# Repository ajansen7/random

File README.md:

# Random Scripts Repository

A collection of various scripts, experiments, and miscellaneous code.

## Projects

### 🧮 Aspens Calculator (`aspens-calculator/`)
- **Purpose**: Computer vision scripts likely for tile or board analysis.
- **Key Tools**: `opencv-python`, `numpy`.
- **Contents**: 
  - Several versions of a calculator (`calc_v*.py`)
  - `training.py` and `training-v2.py` for model training/data collection.
  - `tile-finder.py` for image analysis.

### 🦕 Dino Gen (`dino-gen/`)
- **Purpose**: QR code stitching and image processing, including a Streamlit app.
- **Key Tools**: `streamlit`, `opencv-python`, `pyzbar`.
- **Contents**:
  - `dino_app.py`: Streamlit-based application.
  - `qr_auto_stitch.py`, `qr_manual.py`, `qr_sticter.py`: Tools for QR code processing.

### 🍎 New Fruit (`new-fruit/`)
- **Purpose**: A static web page showcasing fruit/meat hybrids.
- **Key Tools**: HTML, CSS, assets (images and audio).
- **Contents**:
  - `index.html`: The main page.
  - Various image assets like `apple_steak.png` and `banana_sausage.png`.

### 📞 Tattle Phone (`tattle-phone/`)
- **Purpose**: A 3D-printed, toddler-proof 90s-style handset that records "tattles" and uploads them to Google Drive.
- **Key Tools**: ESP32-S3 (Arduino), custom KiCad PCB, Google Apps Script.
- **Contents**:
  - `README.md`: Full design doc (architecture, BOM, power, PCB, enclosure, build plan).
  - `firmware/tattle_phone/`: Record/upload firmware.
  - `cloud/drive_upload.gs`: Drive upload receiver with email notification.

## Setup

### Python Dependencies
To install the necessary Python libraries:

```bash
pip install -r requirements.txt
```

Note: `pyzbar` may require additional system-level libraries (e.g., `libzbar-dev` on Linux or `zbar` via Homebrew on macOS).

## Contributing
Feel free to add your own random scripts or improve existing ones!

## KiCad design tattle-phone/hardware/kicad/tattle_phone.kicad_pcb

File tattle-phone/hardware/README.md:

# Tattle Phone: PCB

There's a KiCad project in [`kicad/`](kicad/). It has a schematic with every part
and connection, and a **routed** board: outline, placement fitted to the printed
case, ~1,800 track segments and ~260 vias, GND pours on both layers and the antenna keep-out.

**6 connections are still open.** They're in tight spots where the autorouter and my
fix-up router couldn't get through without shoving other traces aside. KiCad's
interactive router does that easily. **[KICAD_GUIDE.md](KICAD_GUIDE.md) walks a first-time
user through each one with a close-up picture.** After that, `kicad_gen/make_fab.py`
generates the factory files.

> ⚠️ Component values come from datasheets and common reference designs
> (Adafruit's BQ24075 and MAX98357A boards are worth opening alongside). Check
> them, and the footprints, against current datasheets before ordering. This
> board hasn't been built.

## Files

| File | What it is |
|---|---|
| `kicad/tattle_phone.kicad_pro` | Open this in KiCad 10. It was generated with KiCad 7, so 10 will offer to upgrade it; say yes |
| `kicad/tattle_phone.kicad_sch` | One-sheet schematic. Every pin carries a **net label**, so it reads like a netlist. Matching labels are connected |
| `kicad/tattle_phone.kicad_pcb` | Board: outline, placement, nets, pours, keep-out, net classes |
| `kicad/tattle.kicad_sym` | Project symbol library (only the MAX17048; everything else is stock KiCad) |
| `kicad_gen/design.py` | **The circuit as code:** every part, footprint, pin→net and position. This is the master copy |
| `kicad_gen/build.py` | Regenerates the whole KiCad project from `design.py` + `layout.py` |
| `kicad_gen/check.py` | Compares schematic and board pin by pin, then runs DRC and summarises it |
| `kicad_gen/route.py`, `fixup.py` | Autorouting (FreeRouting) and post-route fix-ups; see "How it was routed" |
| `layout.py` | Dimensions shared by the board **and** the 3D-printed case (keys, LEDs, holes, outline) |
| `place_footprints.py` | Scripting-console helper. Re-snaps the case-critical parts if you move things by hand |

### Two ways to work

- **Edit in KiCad (normal):** open the project, finish the last connections, tidy the
  schematic. From then on the KiCad files are the master copy, and `design.py` becomes reference.
  Don't re-run `build.py`, because it would overwrite your routing.
- **Edit the code:** change `design.py` / `layout.py`, run
  `python3 kicad_gen/build.py && python3 kicad_gen/check.py` (needs KiCad's Python
  module), and you get a fresh project. This is good for big part swaps before routing.

## Finishing the routing (KiCad 10)

Open the board, press **B** to refill the pours, then **Inspect → Design Rules Checker**.
It lists the 6 open connections (case coordinates in mm from the bottom-centre of the board):

| Net | Where | What to do |
|---|---|---|
| VBAT | charger U2, pin 2 (≈ −9.6, 18) | Short hop on the back. Nudge the neighbouring trace with the interactive router (X, then drag) |
| GND | ESD chip D1 (≈ 6, 15) | Add a via next to its GND pin, or run a short trace to the nearest GND via |
| GND | speaker-amp corner (≈ 15, 50) | Same: via or short trace to the pour |
| GND | battery gauge U6 area (≈ 16, 57) | Same |
| GND | LED level shifter U8, pin 3 (≈ 9, 74) | Its pin sits in a pocket. Shove one adjacent trace 0.3 mm and drop a via |
| GND | LED power switch Q2 area (≈ 8, 89) | Same |

Then re-run DRC until "unconnected items" reads 0, and do a visual pass. Pay most
attention to the 3.3 V regulator loop (U3/L1/C4–C6) and the USB pair: the autorouter
gets these right electrically, but you can make them shorter and fatter by hand.

**How it was routed** (all scripted, in `kicad_gen/`): `route.py` runs the
[FreeRouting](https://github.com/freerouting/freerouting) autorouter on everything
except GND. `fixup.py` then finishes the leftover signals with a small A* router
(narrowing to 0.15–0.25 mm at fine-pitch pins), finds GND copper islands by rasterizing
the pours, and ties each island to the main ground with a via or short trace.
`fixup.py --cleanup` removes duplicate and dangling vias. Re-running `build.py`
regenerates an **unrouted** board, so only do that if you want to start over.

## Current check results

- **Schematic vs board:** 377 pins, 71 nets, 0 mismatches. KiCad exported the
  schematic's netlist and it was compared pad by pad with the board.
- **DRC:** no clearance, edge, hole or keep-out errors. What's left:
  - *Unconnected items: 6*. See "Finishing the routing" above.
  - *Courtyard overlap LEDn / SWn (12×):* each key LED sits under its keycap, just
    beside the tact switch. The bodies clear by about 0.25 mm; the switch's outline is drawn
    generously.
  - *Library footprint issues:* footprints were placed from KiCad's install
    folder, not through a library table. KiCad 10 may offer to relink them.
  - *Silkscreen:* `tidy.py` places every reference label clear of pads, other labels
    and the edge, and drops artwork nobody can see (LED outlines under the keycaps). A few
    footprint outlines still touch their own pads; KiCad trims those automatically in the Gerbers.
  - *Starved thermals:* a few QFN centre pads have fewer than two ground spokes until routing
    adds vias under them.

## What's on the board

Front (faces the keypad): the 13 tact switches (through-hole) and the 14 RGB LEDs.
Back: everything else.

| Block | Parts | Notes |
|---|---|---|
| USB-C | J1 HRO TYPE-C-31-M-12 (back, mouth at the bottom edge), R1/R2 5.1k CC pull-downs (separate!), F1 polyfuse, D1 USBLC6 ESD, D2 SMF5.0A TVS | Same port charges and flashes the ESP32 |
| Charger | U2 **BQ24075** (power path + SYSOFF), R3–R8, C1–C3, J2 battery JST-PH, J4 NTC JST-PH | ISET 1.2k ≈ 750 mA charge; ILIM 1.5k ≈ 1 A in; R5 (TMR) left unfitted = default safety timers. BQ24075 instead of BQ24074 because it has the SYSOFF pin the power switch needs |
| Power switch | SW14 PCM12 slide, right edge | Drives SYSOFF: OFF disconnects the battery; charging still works |
| Mode switch | SW17 PCM12 slide, left edge → GPIO38 | **TATTLE** = deep sleep, CALL only; **PLAY** = stay on Wi-Fi for intercom |
| 3.3 V | U3 TPS63001 buck-boost, L1 1.5 µH XAL4020, C4–C7 | Footprint has 0.2 mm thermal vias (board min drill set to 0.2 mm) |
| MCU | U1 ESP32-S3-WROOM-1-N16R8 (back, antenna flush with top edge), C8–C11, R9/R10, SW15 RESET, SW16 BOOT | Antenna keep-out zone: no copper in the top ~6 mm |
| Mic | MK1 ICS-43434 (back) + C12, R11 | Port hole through the board lines up with the case's mic duct |
| Amp | U4 MAX98357A, C13/C14, R12, J3 speaker JST-PH | GAIN tied to VDD = 6 dB. J3 sits low on the right; run the speaker leads up the inside of the case |
| Gauge | U6 MAX17048 + C15, R13–R15 (I2C pull-ups) | I2C 0x36 |
| Keypad | SW1–SW12 + U7 **TCA9555RTWR** (QFN, fits between the switch legs), R16, C16; SW13 CALL + R17 | I2C 0x20, internal pull-ups |
| LEDs | LED1 CALL, LED2–13 keys, **LED14 status light**, all SK6812MINI on the front; Q1/Q2 power gate, U8 74AHCT1G125 level shifter, R18–R20, C17/C18, C20–C33 | Chain order matches the firmware: 0 = CALL, 1–12 = keys, 13 = status |
| Test | TP1 TX, TP2 RX, TP3 GND, TP4 VBAT, TP5 VSYS, TP6 3V3, TP7 spare IO1; FID1–3 | |

The pin map matches [`firmware/tattle_phone/pins.h`](../firmware/tattle_phone/pins.h).

## Ordering (JLCPCB or similar)

- 2-layer, 1.6 mm, any colour. Min drill 0.2 mm (thermal vias under U1/U3).
- **Assembly on both sides** (the LEDs are on the front). That costs a bit more
  than one side, but nothing on this board is novice-friendly to hand-solder
  except the through-hole parts.
- **You solder:** 13 tact switches and 3 JST-PH connectors, all big through-hole
  pins. JLC can do these too for a fee.
- Check stock for: ESP32-S3-WROOM-1-N16R8, BQ24075RGTR, TPS63001DRCR,
  MAX98357AETE+T, ICS-43434, MAX17048G+T10, TCA9555RTWR, SK6812MINI, HRO TYPE-C-31-M-12,
  C&K PCM12SMTR. Swap in equivalents in KiCad if any are out of stock.

## Before ordering

1. Finish the 6 connections above, DRC to zero errors.
2. Export a STEP (File → Export → STEP) and drop it into the enclosure model as a fit check.
3. Fabrication outputs: Gerbers + drill files, BOM, and component placement (CPL). See `../ORDERING.md`.

## Bring-up checklist

1. With no battery, plug in USB. Check VIN, VSYS, PGOOD low, and 3V3.
2. Connect the battery. A USB meter should read ~750 mA charge, CHG low. Check that
   the power switch OFF kills VSYS on battery.
3. Flash over USB-C (hold BOOT, tap RESET the first time).
4. Firmware: check the `rms=` mic levels, a test tone, the LEDs, then an upload.
5. Measure deep-sleep current with the switch on TATTLE. Target < 100 µA.

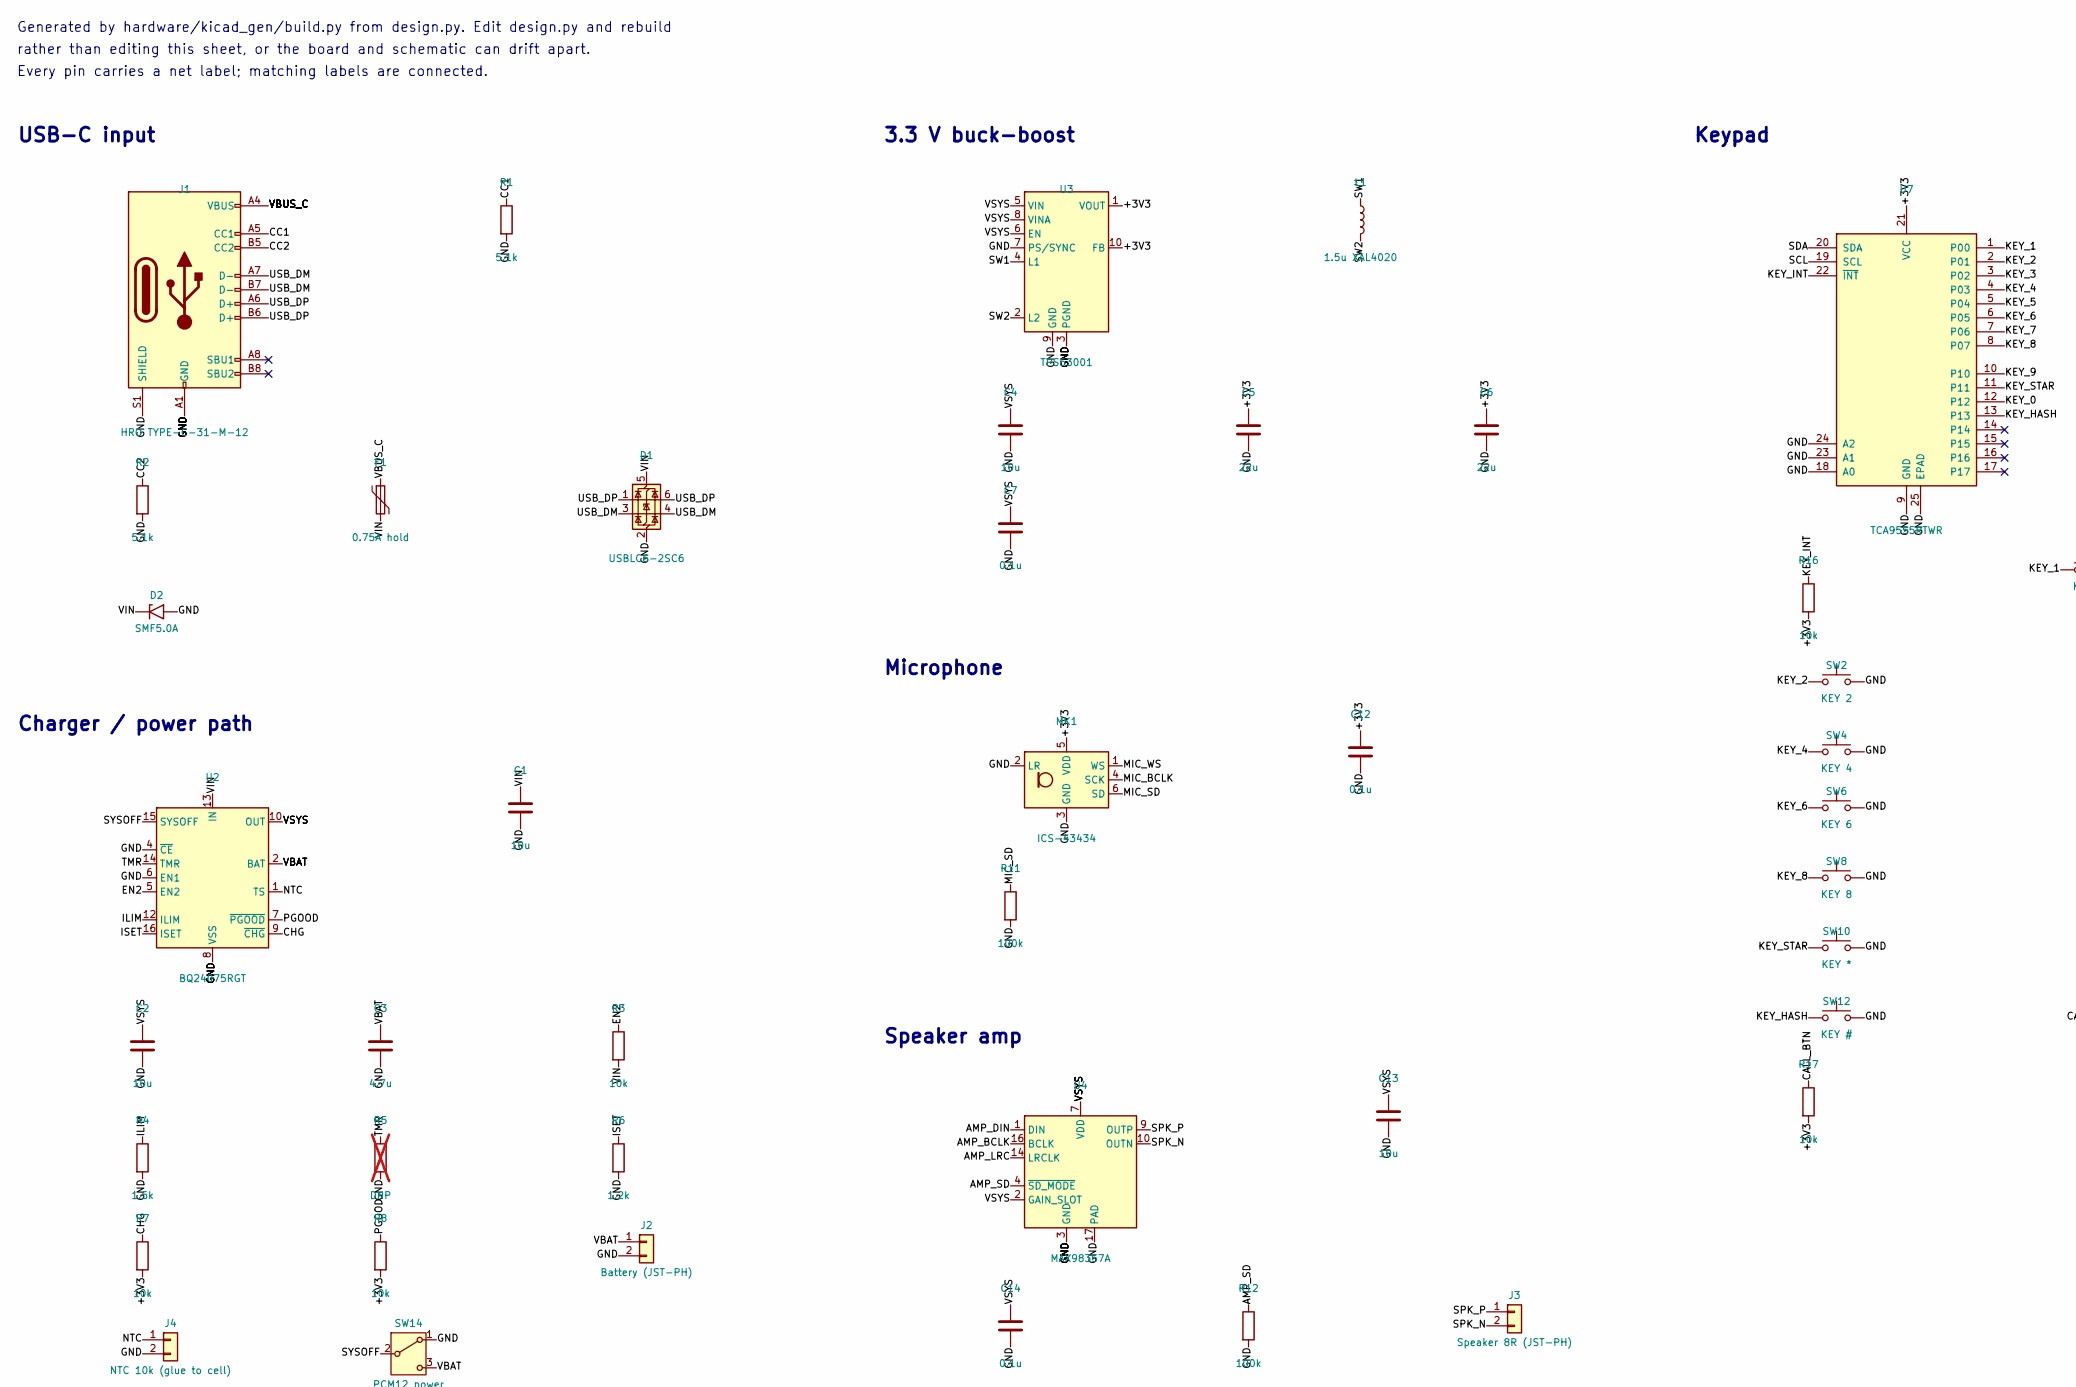
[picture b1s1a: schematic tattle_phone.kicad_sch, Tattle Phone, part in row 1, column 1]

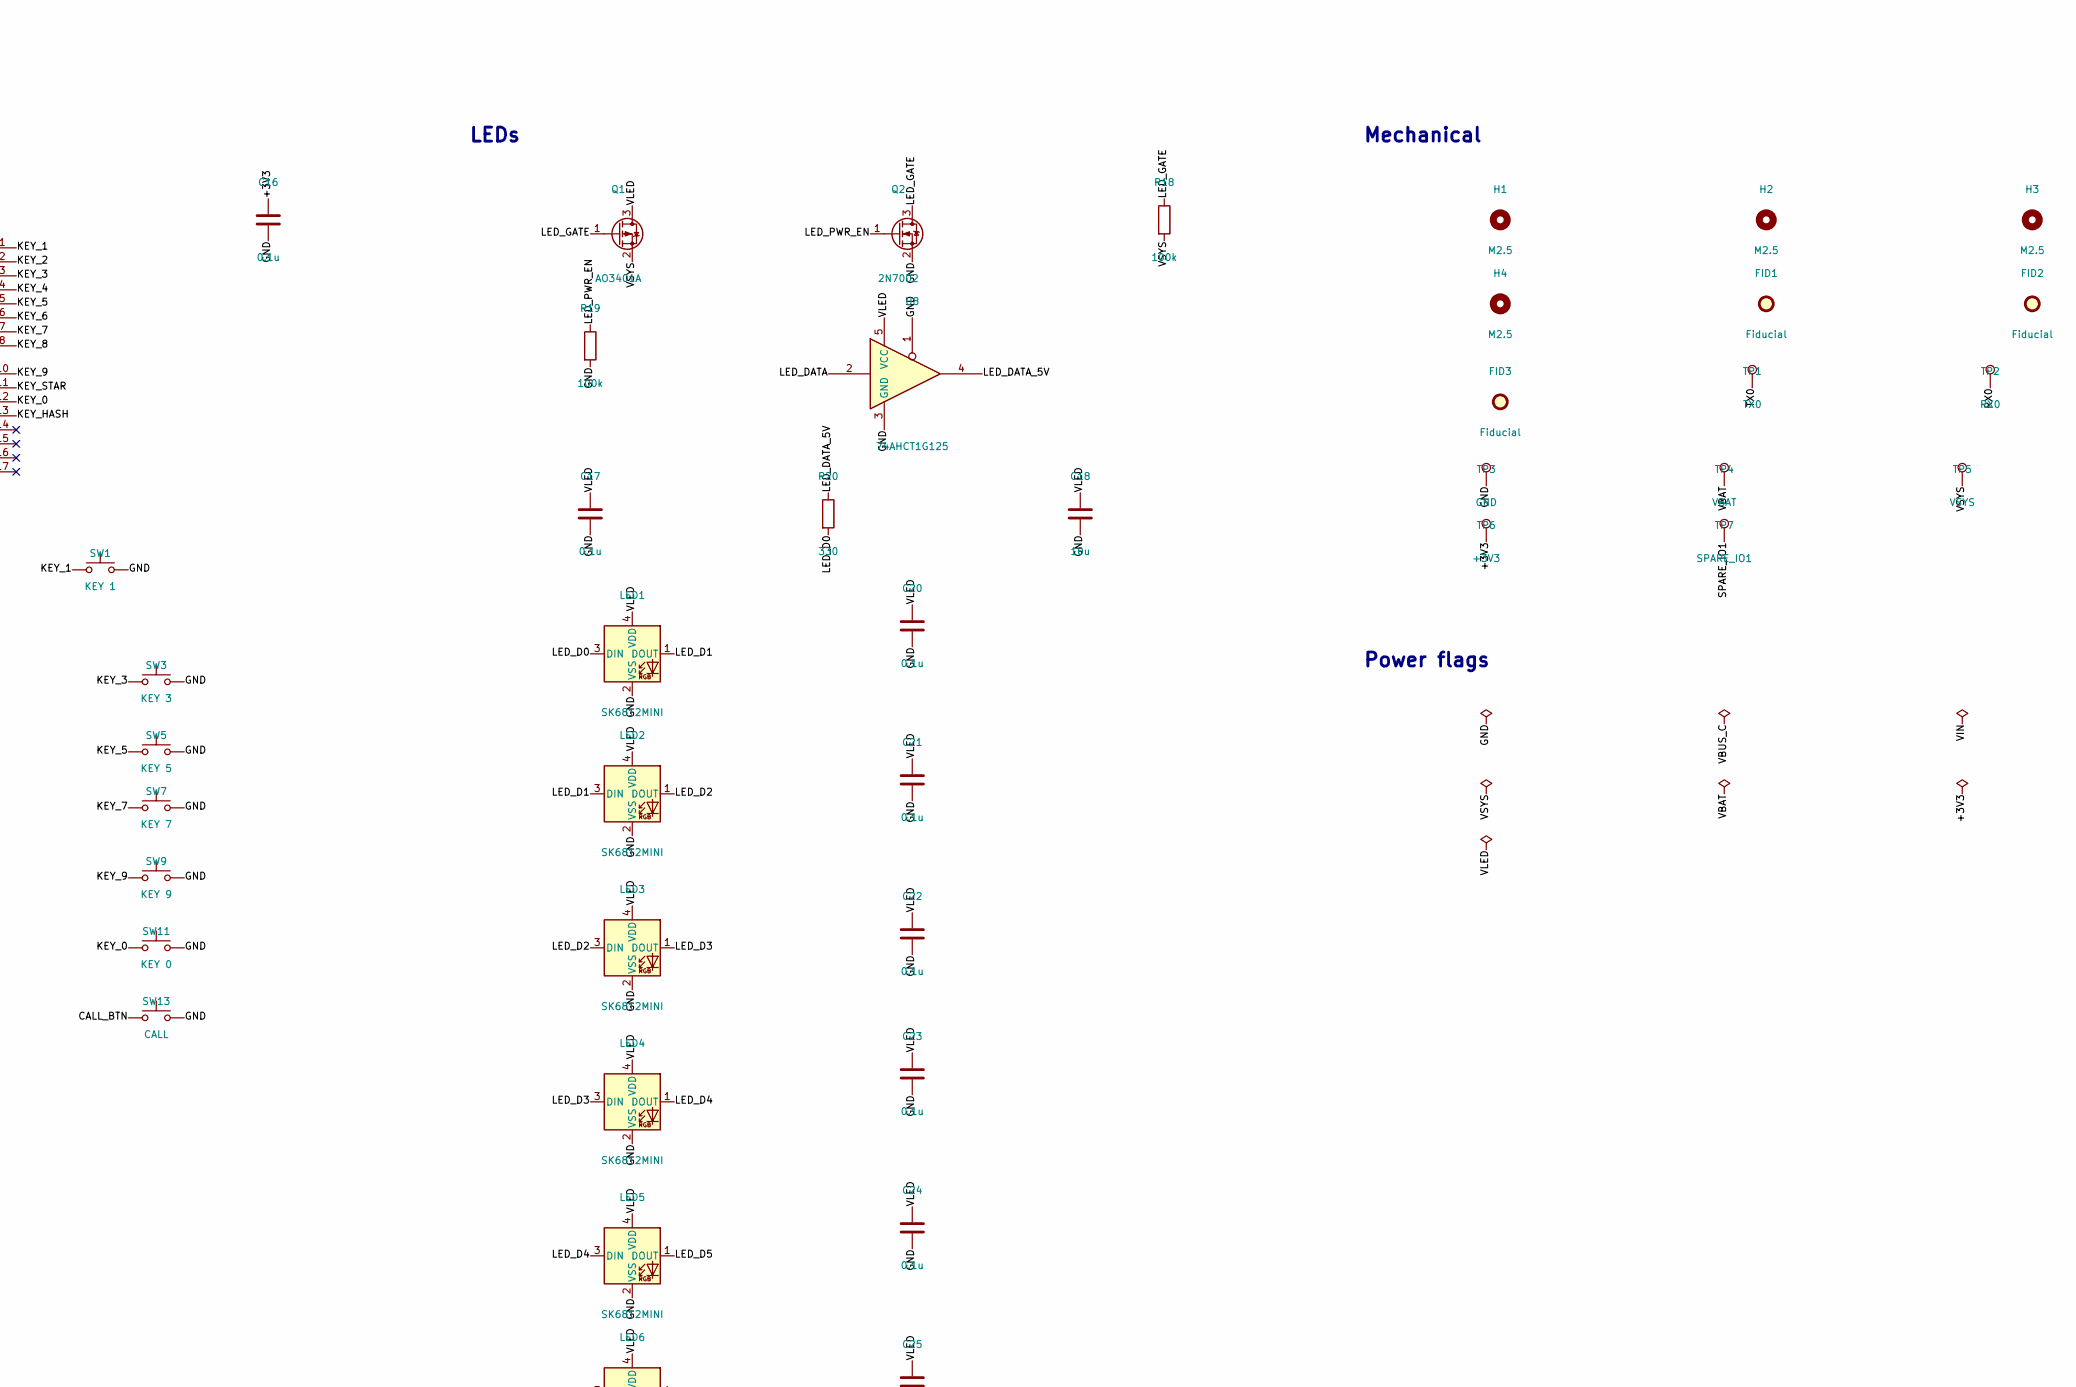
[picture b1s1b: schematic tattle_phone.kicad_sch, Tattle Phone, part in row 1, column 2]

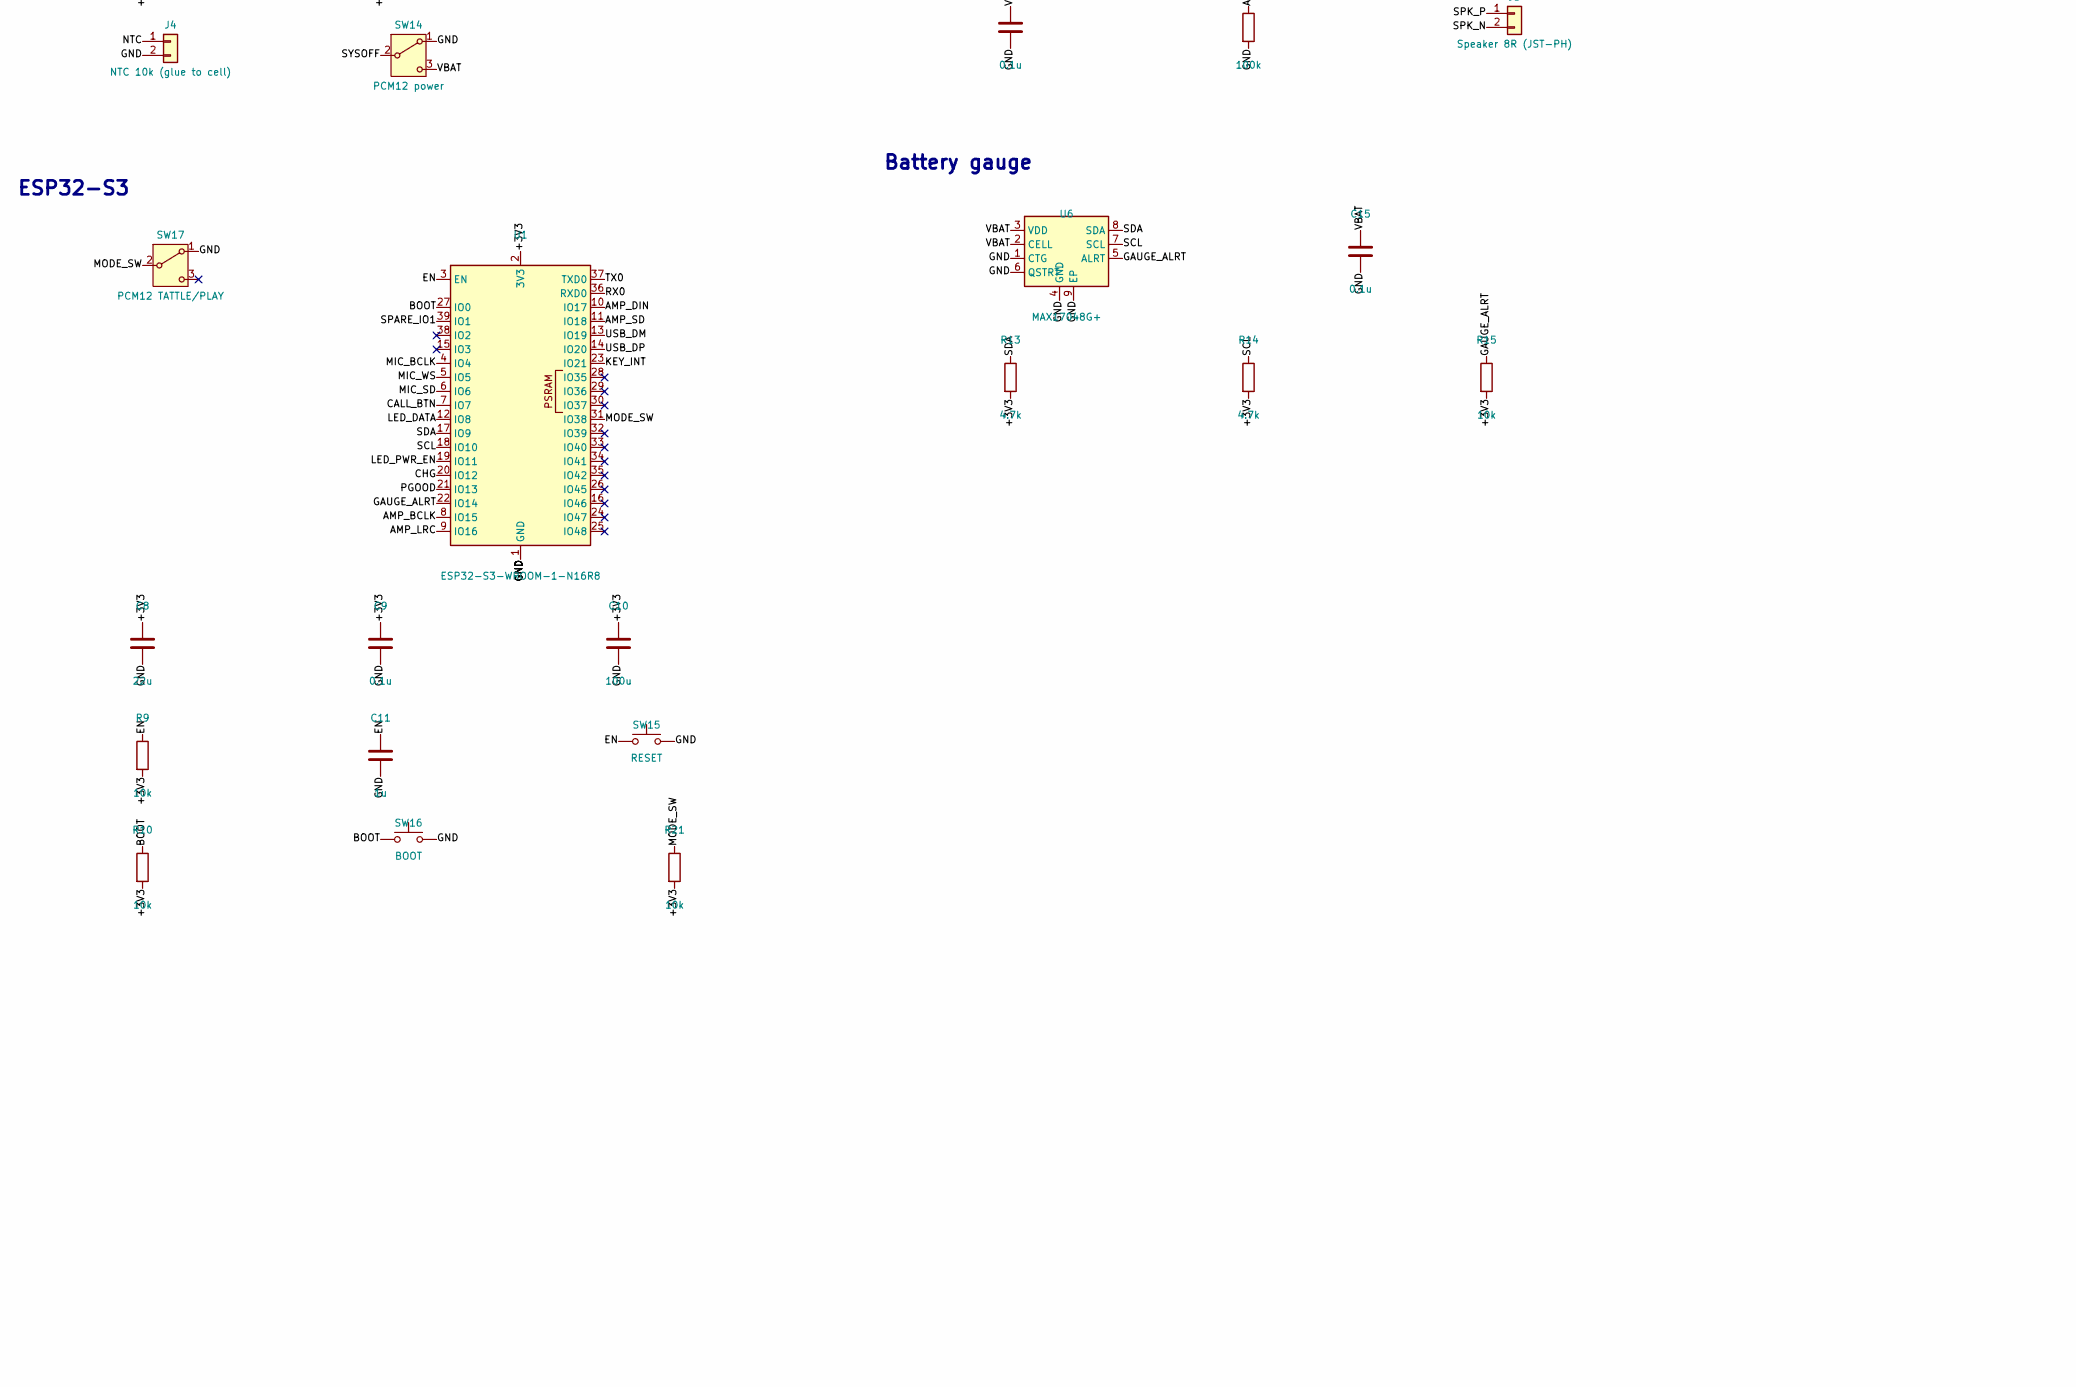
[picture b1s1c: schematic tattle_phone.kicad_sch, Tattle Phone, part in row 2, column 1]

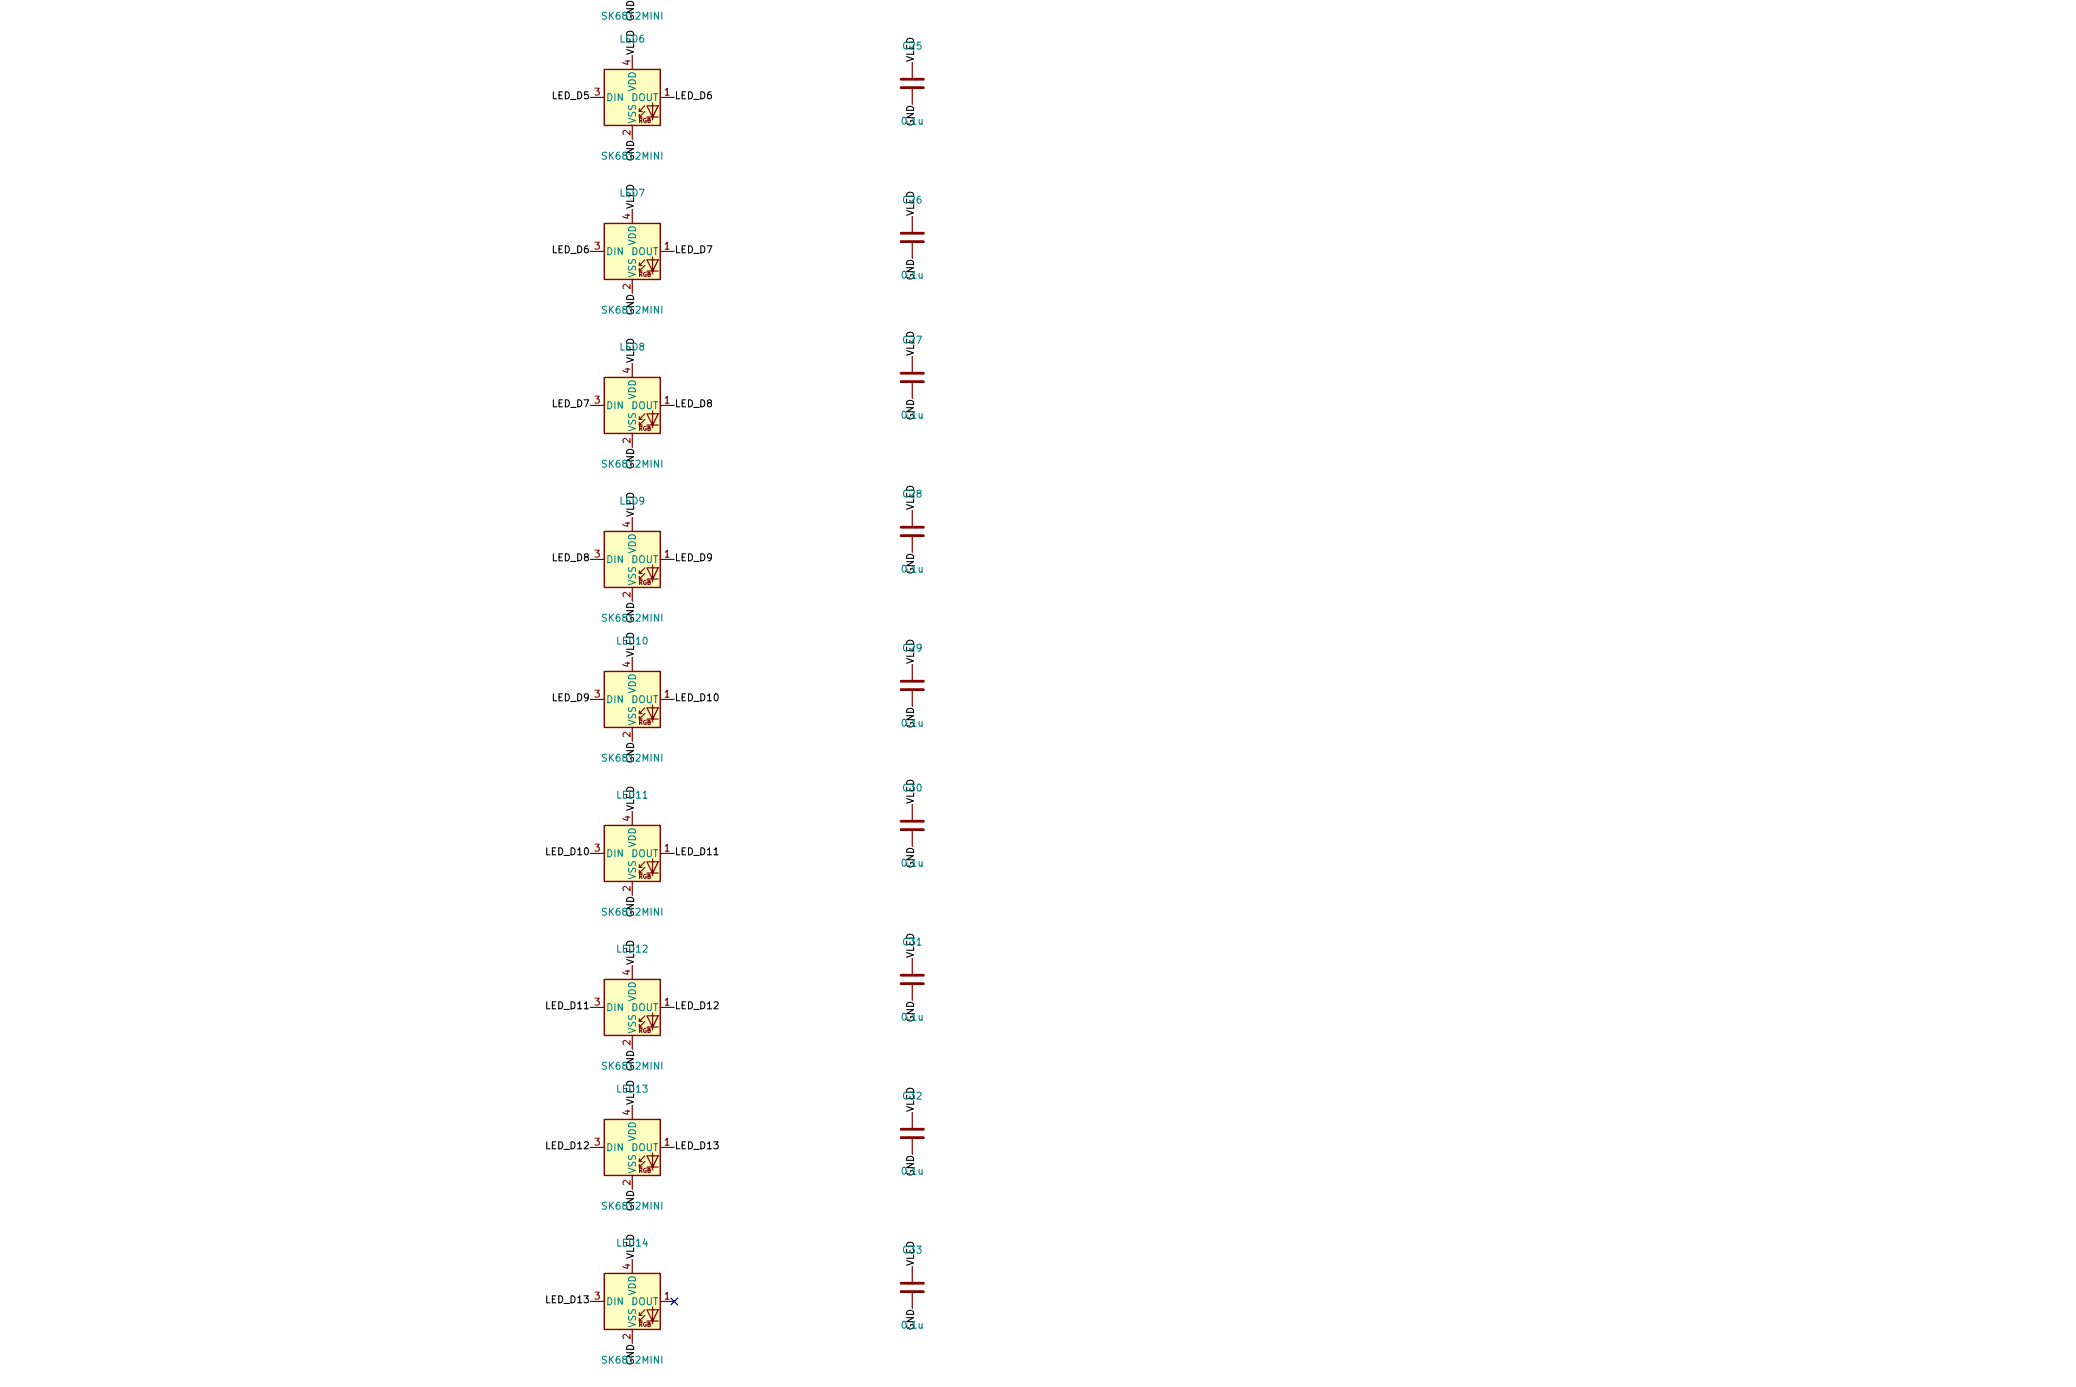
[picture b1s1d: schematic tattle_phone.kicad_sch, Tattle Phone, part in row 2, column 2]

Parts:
C1, C2, C4, C13, C18: 10u; C_0805_2012Metric
C3: 4.7u; C_0603_1608Metric
C5, C6, C8: 22u; C_0805_2012Metric
C7, C9, C12, C14, C15, C16, C17, C20, C21, C22, C23, C24, C25, C26, C27, C28, C29, C30, C31, C32, C33: 0.1u; C_0402_1005Metric
C10: 100u; C_1206_3216Metric
C11: 1u; C_0402_1005Metric
D1: USBLC6-2SC6; SOT-23-6
D2: SMF5.0A; D_SMF
F1: 0.75A hold; Fuse_1206_3216Metric
FID1, FID2, FID3: Fiducial; Fiducial_1mm_Mask2mm
H1, H2, H3, H4: M2.5; MountingHole_2.7mm_M2.5
J1: HRO TYPE-C-31-M-12; USB_C_Receptacle_HRO_TYPE-C-31-M-12
J2: Battery (JST-PH); JST_PH_S2B-PH-K_1x02_P2.00mm_Horizontal
J3: Speaker 8R (JST-PH); JST_PH_S2B-PH-K_1x02_P2.00mm_Horizontal
J4: NTC 10k (glue to cell); JST_PH_S2B-PH-K_1x02_P2.00mm_Horizontal
L1: 1.5u XAL4020; L_Coilcraft_XAL4020-XXX
LED1, LED2, LED3, LED4, LED5, LED6, LED7, LED8, LED9, LED10, LED11, LED12, LED13, LED14: SK6812MINI; LED_SK6812MINI_PLCC4_3.5x3.5mm_P1.75mm
MK1: ICS-43434; InvenSense_ICS-43434-6_3.5x2.65mm
Q1: AO3401A; SOT-23
Q2: 2N7002; SOT-23
R1, R2: 5.1k; R_0402_1005Metric
R3, R7, R8, R9, R10, R15, R16, R17, R21: 10k; R_0402_1005Metric
R4: 1.5k; R_0402_1005Metric
R5: DNP; R_0402_1005Metric; not fitted
R6: 1.2k; R_0402_1005Metric
R11, R12, R18, R19: 100k; R_0402_1005Metric
R13, R14: 4.7k; R_0402_1005Metric
R20: 330; R_0402_1005Metric
SW1: KEY 1; SW_PUSH_6mm_H4.3mm
SW2: KEY 2; SW_PUSH_6mm_H4.3mm
SW3: KEY 3; SW_PUSH_6mm_H4.3mm
SW4: KEY 4; SW_PUSH_6mm_H4.3mm
SW5: KEY 5; SW_PUSH_6mm_H4.3mm
SW6: KEY 6; SW_PUSH_6mm_H4.3mm
SW7: KEY 7; SW_PUSH_6mm_H4.3mm
SW8: KEY 8; SW_PUSH_6mm_H4.3mm
SW9: KEY 9; SW_PUSH_6mm_H4.3mm
SW10: KEY *; SW_PUSH_6mm_H4.3mm
SW11: KEY 0; SW_PUSH_6mm_H4.3mm
SW12: KEY #; SW_PUSH_6mm_H4.3mm
SW13: CALL; SW_PUSH-12mm
SW14: PCM12 power; SW_SPDT_PCM12
SW15: RESET; SW_SPST_B3U-1000P
SW16: BOOT; SW_SPST_B3U-1000P
SW17: PCM12 TATTLE/PLAY; SW_SPDT_PCM12
TP1: TX0; TestPoint_Pad_D1.0mm
TP2: RX0; TestPoint_Pad_D1.0mm
TP3: GND; TestPoint_Pad_D1.0mm
TP4: VBAT; TestPoint_Pad_D1.0mm
TP5: VSYS; TestPoint_Pad_D1.0mm
TP6: +3V3; TestPoint_Pad_D1.0mm
TP7: SPARE_IO1; TestPoint_Pad_D1.0mm
U1: ESP32-S3-WROOM-1-N16R8; ESP32-S3-WROOM-1
U2: BQ24075RGT; VQFN-16-1EP_3x3mm_P0.5mm_EP1.6x1.6mm
U3: TPS63001; Texas_DRC0010J_ThermalVias
U4: MAX98357A; TQFN-16-1EP_3x3mm_P0.5mm_EP1.23x1.23mm
U6: MAX17048G+; TDFN-8-1EP_2x2mm_P0.5mm_EP0.8x1.2mm
U7: TCA9555RTWR; WQFN-24-1EP_4x4mm_P0.5mm_EP2.45x2.45mm
U8: 74AHCT1G125; SOT-23-5

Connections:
+3V3: C5.1, C6.1, C8.1, C9.1, C10.1, C12.1, C16.1, MK1.5 (VDD), R7.2, R8.2, R9.2, R10.2, R13.2, R14.2, R15.2, R16.2, R17.2, R21.2, TP6.1, U1.2 (3V3), U3.1 (VOUT), U3.10 (FB), U7.21 (VCC)
AMP_BCLK: U1.8 (IO15), U4.16 (BCLK)
AMP_DIN: U1.10 (IO17), U4.1 (DIN)
AMP_LRC: U1.9 (IO16), U4.14 (LRCLK)
AMP_SD: R12.1, U1.11 (IO18), U4.4 (~SD_MODE)
BOOT: R10.1, SW16.1, U1.27 (IO0)
CALL_BTN: R17.1, SW13.1, U1.7 (IO7)
CC1: J1.A5 (CC1), R1.1
CC2: J1.B5 (CC2), R2.1
CHG: R7.1, U1.20 (IO12), U2.9 (~CHG)
EN: C11.1, R9.1, SW15.1, U1.3 (EN)
EN2: R3.1, U2.5 (EN2)
GAUGE_ALRT: R15.1, U1.22 (IO14), U6.5 (ALRT)
GND: C1.2, C2.2, C3.2, C4.2, C5.2, C6.2, C7.2, C8.2, C9.2, C10.2, C11.2, C12.2, C13.2, C14.2, C15.2, C16.2, C17.2, C18.2, C20.2, C21.2, C22.2, C23.2, C24.2, C25.2, C26.2, C27.2, C28.2, C29.2, C30.2, C31.2, C32.2, C33.2, D1.2 (GND), D2.2 (A2), J1.A1 (GND), J1.A12 (GND), J1.B1 (GND), J1.B12 (GND), J1.S1 (SHIELD), J2.2, J4.2, LED1.2 (VSS), LED2.2 (VSS), LED3.2 (VSS), LED4.2 (VSS), LED5.2 (VSS), LED6.2 (VSS), LED7.2 (VSS), LED8.2 (VSS), LED9.2 (VSS), LED10.2 (VSS), LED11.2 (VSS), LED12.2 (VSS), LED13.2 (VSS), LED14.2 (VSS), MK1.2 (LR), MK1.3 (GND), Q2.2 (S), R1.2, R2.2, R4.2, R5.2, R6.2, R11.2, R12.2, R19.2, SW1.2, SW2.2, SW3.2, SW4.2, SW5.2, SW6.2, SW7.2, SW8.2, SW9.2, SW10.2, SW11.2, SW12.2, SW13.2, SW14.1 (A), SW15.2, SW16.2, SW17.1 (A), TP3.1, U1.1 (GND), U1.40 (GND), U1.41 (GND), U2.4 (~CE), U2.6 (EN1), U2.8 (VSS), U2.17 (VSS), U3.3 (PGND), U3.7 (PS/SYNC), U3.9 (GND), U3.11 (PGND), U4.3 (GND), U4.11 (GND), U4.15 (GND), U4.17 (PAD), U6.1 (CTG), U6.4 (GND), U6.6 (QSTRT), U6.9 (EP), U7.9 (GND), U7.18 (A0), U7.23 (A1), U7.24 (A2), U7.25 (EPAD), U8.1, U8.3 (GND)
ILIM: R4.1, U2.12 (ILIM)
ISET: R6.1, U2.16 (ISET)
KEY_0: SW11.1, U7.12
KEY_1: SW1.1, U7.1 (P00)
KEY_2: SW2.1, U7.2 (P01)
KEY_3: SW3.1, U7.3 (P02)
KEY_4: SW4.1, U7.4 (P03)
KEY_5: SW5.1, U7.5 (P04)
KEY_6: SW6.1, U7.6 (P05)
KEY_7: SW7.1, U7.7 (P06)
KEY_8: SW8.1, U7.8 (P07)
KEY_9: SW9.1, U7.10
KEY_HASH: SW12.1, U7.13
KEY_INT: R16.1, U1.23 (IO21), U7.22 (~INT)
KEY_STAR: SW10.1, U7.11
LED_D0: LED1.3 (DIN), R20.2
LED_D1: LED1.1 (DOUT), LED2.3 (DIN)
LED_D2: LED2.1 (DOUT), LED3.3 (DIN)
LED_D3: LED3.1 (DOUT), LED4.3 (DIN)
LED_D4: LED4.1 (DOUT), LED5.3 (DIN)
LED_D5: LED5.1 (DOUT), LED6.3 (DIN)
LED_D6: LED6.1 (DOUT), LED7.3 (DIN)
LED_D7: LED7.1 (DOUT), LED8.3 (DIN)
LED_D8: LED8.1 (DOUT), LED9.3 (DIN)
LED_D9: LED9.1 (DOUT), LED10.3 (DIN)
LED_D10: LED10.1 (DOUT), LED11.3 (DIN)
LED_D11: LED11.1 (DOUT), LED12.3 (DIN)
LED_D12: LED12.1 (DOUT), LED13.3 (DIN)
LED_D13: LED13.1 (DOUT), LED14.3 (DIN)
LED_DATA: U1.12 (IO8), U8.2
LED_DATA_5V: R20.1, U8.4
LED_GATE: Q1.1 (G), Q2.3 (D), R18.1
LED_PWR_EN: Q2.1 (G), R19.1, U1.19 (IO11)
MIC_BCLK: MK1.4 (SCK), U1.4 (IO4)
MIC_SD: MK1.6 (SD), R11.1, U1.6 (IO6)
MIC_WS: MK1.1 (WS), U1.5 (IO5)
MODE_SW: R21.1, SW17.2 (B), U1.31 (IO38)
NTC: J4.1, U2.1 (TS)
PGOOD: R8.1, U1.21 (IO13), U2.7 (~PGOOD)
RX0: TP2.1, U1.36 (RXD0)
SCL: R14.1, U1.18 (IO10), U6.7 (SCL), U7.19 (SCL)
SDA: R13.1, U1.17 (IO9), U6.8 (SDA), U7.20 (SDA)
SPARE_IO1: TP7.1, U1.39 (IO1)
SPK_N: J3.2, U4.10 (OUTN)
SPK_P: J3.1, U4.9 (OUTP)
SW1: L1.1, U3.4 (L1)
SW2: L1.2, U3.2 (L2)
SYSOFF: SW14.2 (B), U2.15 (SYSOFF)
TMR: R5.1, U2.14 (TMR)
TX0: TP1.1, U1.37 (TXD0)
USB_DM: D1.3 (I/O2), D1.4 (I/O2), J1.A7 (D-), J1.B7 (D-), U1.13 (IO19)
USB_DP: D1.1 (I/O1), D1.6 (I/O1), J1.A6 (D+), J1.B6 (D+), U1.14 (IO20)
VBAT: C3.1, C15.1, J2.1, SW14.3 (C), TP4.1, U2.2 (BAT), U2.3 (BAT), U6.2 (CELL), U6.3 (VDD)
VBUS_C: F1.1, J1.A4 (VBUS), J1.A9 (VBUS), J1.B4 (VBUS), J1.B9 (VBUS)
VIN: C1.1, D1.5 (VBUS), D2.1 (A1), F1.2, R3.2, U2.13 (IN)
VLED: C17.1, C18.1, C20.1, C21.1, C22.1, C23.1, C24.1, C25.1, C26.1, C27.1, C28.1, C29.1, C30.1, C31.1, C32.1, C33.1, LED1.4 (VDD), LED2.4 (VDD), LED3.4 (VDD), LED4.4 (VDD), LED5.4 (VDD), LED6.4 (VDD), LED7.4 (VDD), LED8.4 (VDD), LED9.4 (VDD), LED10.4 (VDD), LED11.4 (VDD), LED12.4 (VDD), LED13.4 (VDD), LED14.4 (VDD), Q1.3 (D), U8.5 (VCC)
VSYS: C2.1, C4.1, C7.1, C13.1, C14.1, Q1.2 (S), R18.2, TP5.1, U2.10 (OUT), U2.11 (OUT), U3.5 (VIN), U3.6 (EN), U3.8 (VINA), U4.2 (GAIN_SLOT), U4.7 (VDD), U4.8 (VDD)

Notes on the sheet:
USB-C input
Charger / power path
ESP32-S3
3.3 V buck-boost
Microphone
Speaker amp
Battery gauge
Keypad
LEDs
Mechanical
Power flags
Generated by hardware/kicad_gen/build.py from design.py. Edit design.py and rebuild
rather than editing this sheet, or the board and schematic can drift apart.
Every pin carries a net label; matching labels are connected.

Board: 2 copper layers, 116 parts (85 on the bottom side), 71 nets, no tracks yet.

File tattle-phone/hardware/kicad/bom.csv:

Comment,Designator,Footprint,Qty,Side,Assembly,LCSC Part #
HRO TYPE-C-31-M-12,J1,USB_C_Receptacle_HRO_TYPE-C-31-M-12,1,Back,factory,
5.1k,"R1,R2",R_0402_1005Metric,2,Back,factory,
0.75A hold,F1,Fuse_1206_3216Metric,1,Back,factory,
USBLC6-2SC6,D1,SOT-23-6,1,Back,factory,
SMF5.0A,D2,D_SMF,1,Back,factory,
BQ24075RGT,U2,VQFN-16-1EP_3x3mm_P0.5mm_EP1.6x1.6mm,1,Back,factory,
10u,"C1,C2,C4,C13,C18",C_0805_2012Metric,5,Back,factory,
4.7u,C3,C_0603_1608Metric,1,Back,factory,
10k,"R3,R7,R8,R9,R10,R21,R15,R16,R17",R_0402_1005Metric,9,Back,factory,
1.5k,R4,R_0402_1005Metric,1,Back,factory,
DNP,R5,R_0402_1005Metric,1,Back,DO NOT FIT,
1.2k,R6,R_0402_1005Metric,1,Back,factory,
Battery (JST-PH),J2,JST_PH_S2B-PH-K_1x02_P2.00mm_Horizontal,1,Back,hand-solder (through-hole),
NTC 10k (glue to cell),J4,JST_PH_S2B-PH-K_1x02_P2.00mm_Horizontal,1,Back,hand-solder (through-hole),
PCM12 power,SW14,SW_SPDT_PCM12,1,Back,factory,
PCM12 TATTLE/PLAY,SW17,SW_SPDT_PCM12,1,Back,factory,
TPS63001,U3,Texas_DRC0010J_ThermalVias,1,Back,factory,
1.5u XAL4020,L1,L_Coilcraft_XAL4020-XXX,1,Back,factory,
22u,"C5,C6,C8",C_0805_2012Metric,3,Back,factory,
0.1u,"C7,C9,C12,C14,C15,C16,C17,C20,C21,C22,C23,C24,C25,C26,C27,C28,C29,C30,C31,C32,C33",C_0402_1005Metric,21,Back,factory,
ESP32-S3-WROOM-1-N16R8,U1,ESP32-S3-WROOM-1,1,Back,factory,
100u,C10,C_1206_3216Metric,1,Back,factory,
1u,C11,C_0402_1005Metric,1,Back,factory,
RESET,SW15,SW_SPST_B3U-1000P,1,Back,factory,
BOOT,SW16,SW_SPST_B3U-1000P,1,Back,factory,
ICS-43434,MK1,InvenSense_ICS-43434-6_3.5x2.65mm,1,Back,factory,
100k,"R11,R12,R18,R19",R_0402_1005Metric,4,Back,factory,
MAX98357A,U4,TQFN-16-1EP_3x3mm_P0.5mm_EP1.23x1.23mm,1,Back,factory,
Speaker 8R (JST-PH),J3,JST_PH_S2B-PH-K_1x02_P2.00mm_Horizontal,1,Back,hand-solder (through-hole),
MAX17048G+,U6,TDFN-8-1EP_2x2mm_P0.5mm_EP0.8x1.2mm,1,Back,factory,
4.7k,"R13,R14",R_0402_1005Metric,2,Back,factory,
TCA9555RTWR,U7,WQFN-24-1EP_4x4mm_P0.5mm_EP2.45x2.45mm,1,Back,factory,
KEY 1,SW1,SW_PUSH_6mm_H4.3mm,1,Front,hand-solder (through-hole),
KEY 2,SW2,SW_PUSH_6mm_H4.3mm,1,Front,hand-solder (through-hole),
KEY 3,SW3,SW_PUSH_6mm_H4.3mm,1,Front,hand-solder (through-hole),
KEY 4,SW4,SW_PUSH_6mm_H4.3mm,1,Front,hand-solder (through-hole),
KEY 5,SW5,SW_PUSH_6mm_H4.3mm,1,Front,hand-solder (through-hole),
KEY 6,SW6,SW_PUSH_6mm_H4.3mm,1,Front,hand-solder (through-hole),
KEY 7,SW7,SW_PUSH_6mm_H4.3mm,1,Front,hand-solder (through-hole),
KEY 8,SW8,SW_PUSH_6mm_H4.3mm,1,Front,hand-solder (through-hole),
KEY 9,SW9,SW_PUSH_6mm_H4.3mm,1,Front,hand-solder (through-hole),
KEY *,SW10,SW_PUSH_6mm_H4.3mm,1,Front,hand-solder (through-hole),
KEY 0,SW11,SW_PUSH_6mm_H4.3mm,1,Front,hand-solder (through-hole),
KEY #,SW12,SW_PUSH_6mm_H4.3mm,1,Front,hand-solder (through-hole),
CALL,SW13,SW_PUSH-12mm,1,Front,hand-solder (through-hole),
AO3401A,Q1,SOT-23,1,Back,factory,
2N7002,Q2,SOT-23,1,Back,factory,
74AHCT1G125,U8,SOT-23-5,1,Back,factory,
330,R20,R_0402_1005Metric,1,Back,factory,
SK6812MINI,"LED1,LED2,LED3,LED4,LED5,LED6,LED7,LED8,LED9,LED10,LED11,LED12,LED13,LED14",LED_SK6812MINI_PLCC4_3.5x3.5mm_P1.75mm,14,Front,factory,

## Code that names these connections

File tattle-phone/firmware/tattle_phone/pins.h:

// Pin map for the ESP32-S3 (WROOM-1 N16R8). The same map is used on the
// breadboard prototype and the custom PCB, so firmware carries over unchanged.
//
// Avoided on purpose: GPIO0/3/45/46 (strapping), GPIO19/20 (native USB, used
// for flashing over the USB-C port), GPIO35-37 (octal PSRAM on R8 modules).
#pragma once

// I2S microphone (INMP441 / ICS-43434). Tie the mic's L/R pin to GND (= left).
#define PIN_MIC_BCLK  4
#define PIN_MIC_WS    5
#define PIN_MIC_SD    6

// I2S amplifier (MAX98357A)
#define PIN_AMP_BCLK  15
#define PIN_AMP_LRC   16
#define PIN_AMP_DIN   17
#define PIN_AMP_SD    18   // amp shutdown: LOW = off (saves ~2 mA and kills hiss)

// The big "CALL" button (to GND, internal pull-up). Must be an RTC GPIO (0-21)
// so it can wake the chip from deep sleep.
#define PIN_CALL_BTN  7

// Addressable LED chain (SK6812MINI). LED 0 = call button, 1-12 = keypad 1..9 * 0 #,
// 13 = status ("in use") light above the keypad.
#define PIN_LEDS      8
#define NUM_LEDS      14
#define LED_STATUS    13
// Drives a P-MOSFET high-side switch on the LED 5V/VBAT rail. WS2812s draw
// ~1 mA each even when "off", which would flatten the battery in deep sleep.
#define PIN_LED_PWR   11   // HIGH = LEDs powered

// Battery voltage via 2:1 divider (only needed if you skip the MAX17048 gauge)
#define PIN_VBAT_ADC  1

// I2C bus: fuel gauge (MAX17048 @0x36) + keypad expander (TCA9555 @0x20)
#define PIN_I2C_SDA   9
#define PIN_I2C_SCL   10

// Charger status (BQ24075 open-drain outputs, pulled up to 3V3; LOW = active)
#define PIN_CHG       12   // LOW while charging
#define PIN_PGOOD     13   // LOW when USB power is present
#define PIN_GAUGE_ALRT 14  // MAX17048 low-battery alert (optional)
#define PIN_KEYPAD_INT 21  // TCA9555 INT; RTC GPIO so a key press can wake the phone
#define PIN_MODE_SW   38   // TATTLE/PLAY slide switch: LOW = PLAY (stay reachable), HIGH = TATTLE only

// Backup serial on test pads: GPIO43 (TX) / GPIO44 (RX)

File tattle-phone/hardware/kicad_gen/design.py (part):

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     {"Pin_1": "VBAT", "Pin_2": "GND"}, at=(-18.5, 33.0), block=B,
     note="check your cell's lead polarity")
part("J4", "Connector_Generic:Conn_01x02", "NTC 10k (glue to cell)", JST2,
     {"Pin_1": "NTC", "Pin_2": "GND"}, at=(-18.5, 43.0), block=B)
part("SW14", "Switch:SW_SPDT", "PCM12 power", "Button_Switch_SMD:SW_SPDT_PCM12",
     {"A": "GND", "B": "SYSOFF", "C": "VBAT"},
     at=(LY.PCB_CORNERS[1][0] + 1.4, LY.SLIDE_SWITCH_Y), block=B,
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C("C14", "0.1u", "VSYS", at=(5.5, 43.0), block=B)
R("R12", "100k", "AMP_SD", "GND", at=(5.5, 46.5), block=B)
part("J3", "Connector_Generic:Conn_01x02", "Speaker 8R (JST-PH)", JST2,
     {"Pin_1": "SPK_P", "Pin_2": "SPK_N"}, at=(18.5, 33.0), block=B,
     note="speaker leads run up the inside of the case to the earpiece")

# ======================================================================= battery gauge
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key_nets = ["KEY_1", "KEY_2", "KEY_3", "KEY_4", "KEY_5", "KEY_6", "KEY_7", "KEY_8", "KEY_9",
            "KEY_STAR", "KEY_0", "KEY_HASH"]
io_pins = [f"P0{i}" for i in range(8)] + [f"P1{i}" for i in range(4)]
pins = {"~{INT}": "KEY_INT", "A0": "GND", "A1": "GND", "A2": "GND", "GND": "GND", "EPAD": "GND",
        "VCC": "+3V3", "SCL": "SCL", "SDA": "SDA"}
pins.update({p: n for p, n in zip(io_pins, key_nets)})
part("U7", "Interface_Expansion:TCA9555RTWR", "TCA9555RTWR",
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
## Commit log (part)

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2026-02-26 Initialize project configuration: .gitignore, LICENSE, requirements.txt, and enhanced README.md
2026-02-26 Audit: Add READMEs, LICENSEs, fix typos, and restructure dino-gen/qr-tools
2026-02-26 added a nifty little audio recording tool
2026-02-26 docs: ignore interview recorder outputs and remove existing recordings
2026-02-26 feat: add cancel recording functionality with Esc key
2026-02-26 fix: reduce transcription hallucinations by trimming end audio and adjusting whisper params
